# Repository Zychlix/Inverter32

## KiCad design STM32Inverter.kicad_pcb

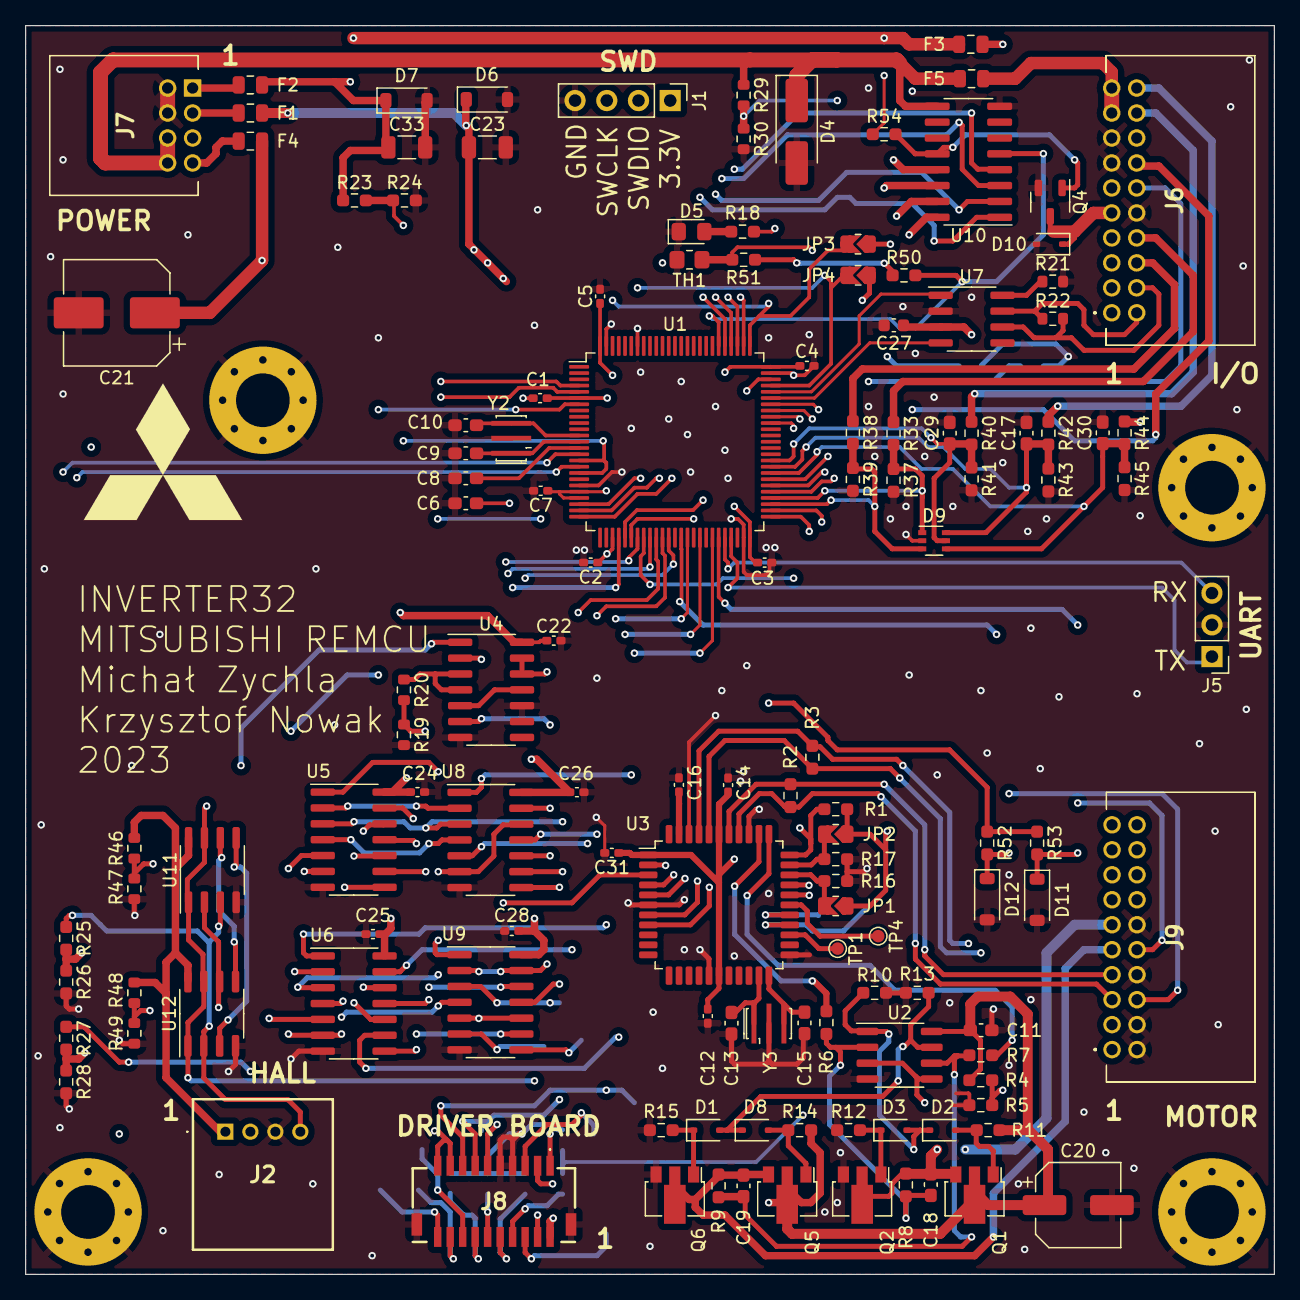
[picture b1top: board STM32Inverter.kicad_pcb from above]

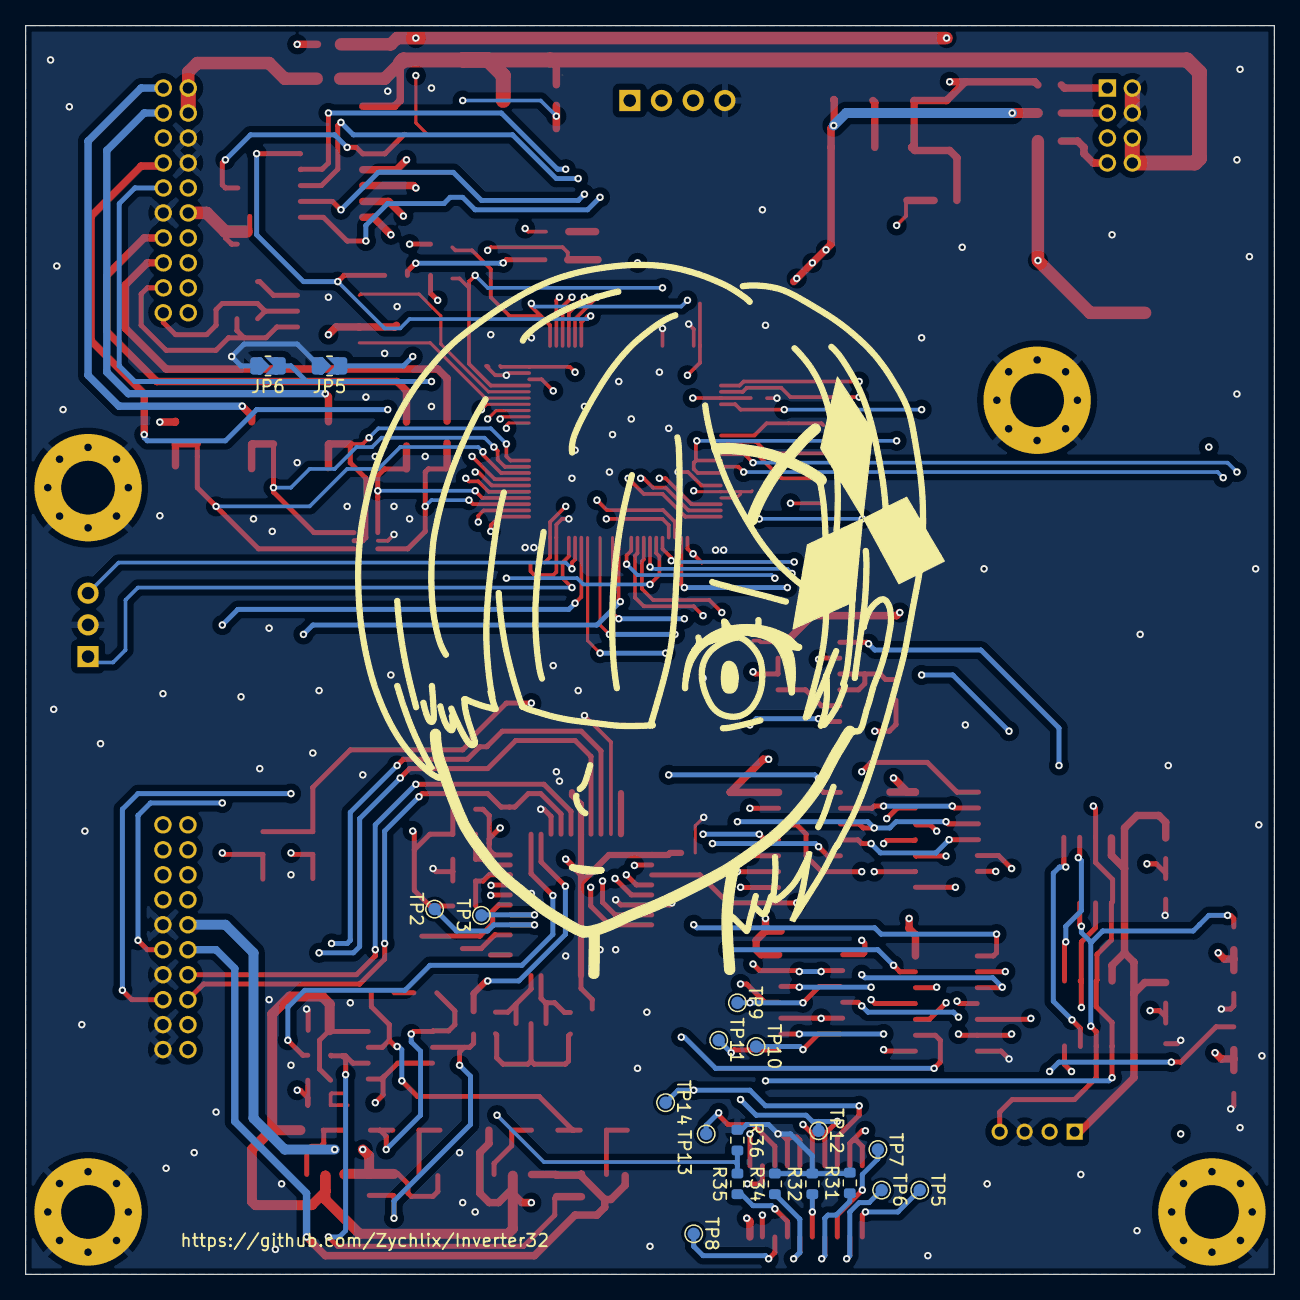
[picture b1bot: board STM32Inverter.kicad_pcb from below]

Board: 4 copper layers, 100.0 x 100.0 mm, 154 parts (19 on the bottom side), 137 nets.

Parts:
C1, C2, C3, C4, C5, C7, C12, C14, C16, C22, C24, C25, C26, C28, C31: 1u; C_0402_1005Metric_Pad0.74x0.62mm_HandSolder
C6: 10n; C_0603_1608Metric_Pad1.08x0.95mm_HandSolder
C8, C11, C17, C29, C30: 100n; C_0603_1608Metric_Pad1.08x0.95mm_HandSolder
C9, C10, C13, C15: DNP; C_0603_1608Metric_Pad1.08x0.95mm_HandSolder
C18, C19: 100p; C_0603_1608Metric_Pad1.08x0.95mm_HandSolder
C20: 100u; CP_Elec_6.3x7.7
C21: 100uF 25V; CP_Elec_8x6.2
C23, C33: 22uF 10V; C_1206_3216Metric
C27: 100nF; C_0603_1608Metric
D1, D2, D3, D8, D10: 1N4148; D_SOD-323
D4: 1N4007; D_SMA_Handsoldering
D5: LED; LED_0805_2012Metric_Pad1.15x1.40mm_HandSolder
D6, D11, D12: BZT52C3V6; D_SOD-123
D7: BZT52C5V6; D_SOD-123
D9: PESD3V3L5UY; SOT-363_SC-70-6
F1, F2, F3, F4: 350mA; Fuse_0805_2012Metric
F5: 2A; Fuse_0805_2012Metric
H1, H2, H3, H4: MountingHole_Pad; MountingHole_4.3mm_M4_Pad_Via
J1: STLINK; PinHeader_1x04_P2.54mm_Vertical
J2: CURRENT SENSE; DF51K4P2DS805
J5: UART; PinHeader_1x03_P2.54mm_Vertical
J6: INTERFACE; DF51K20DP2DS805
J7: POWER; DF51K8DP2DS805
J8: 501571-2007; 5015712007
J9: RESOLVER; DF51K20DP2DS805
JP1, JP2, JP3, JP4, JP5, JP6: R_0805_2012Metric_Jumper
Q1, Q5: BCX54; SOT-89-3
Q2, Q6: BCX55; SOT-89-3
Q4: ST3422A; SOT-23-3
R1: 4.7k; R_0603_1608Metric_Pad0.98x0.95mm_HandSolder
R2, R3: 68k; R_0603_1608Metric_Pad0.98x0.95mm_HandSolder
R4, R5: 22k; R_0603_1608Metric_Pad0.98x0.95mm_HandSolder
R6, R7, R8, R9, R16, R17, R23, R24, R25, R26, R27, R28, R33, R37, R38, R39, R40, R42, R44, R51, R52, R53: 10k; R_0603_1608Metric_Pad0.98x0.95mm_HandSolder
R10, R11, R12, R13, R14, R15, R41, R43, R45, R50, R54: 2.2k; R_0603_1608Metric_Pad0.98x0.95mm_HandSolder
R18: 470; R_0603_1608Metric_Pad0.98x0.95mm_HandSolder
R19, R30, R31, R32, R34, R36: 4.7k; R_0603_1608Metric
R20, R29, R35: 2.7k; R_0603_1608Metric
R21: 1k; R_0603_1608Metric
R22: 120; R_0603_1608Metric
R46, R47, R48, R49: R_0603_1608Metric
TH1: Thermistor_NTC; R_0805_2012Metric_Pad1.20x1.40mm_HandSolder
TP1: A; TestPoint_Pad_D1.0mm
TP2: B; TestPoint_Pad_D1.0mm
TP3: NM; TestPoint_Pad_D1.0mm
TP4: DIR; TestPoint_Pad_D1.0mm
TP5, TP6, TP7, TP8, TP9, TP10, TP11, TP12, TP13, TP14: TestPoint; TestPoint_Pad_D1.0mm
U1: STM32F303VCTx; LQFP-100_14x14mm_P0.5mm
U2: LM358; SO-8_3.9x4.9mm_P1.27mm
U3: AD2S1205; LQFP-44_10x10mm_P0.8mm
U4: 74HCT00; SOIC-14_3.9x8.7mm_P1.27mm
U5: 74HCT04; SOIC-14_3.9x8.7mm_P1.27mm
U6, U8, U9: 74HCT08; SOIC-14_3.9x8.7mm_P1.27mm
U7: MCP2551-I-SN; SOIC-8_3.9x4.9mm_P1.27mm
U10: ULN2002; SOP-16_3.9x9.9mm_P1.27mm
U11, U12: LM393; SO-8_3.9x4.9mm_P1.27mm
Y2, Y3: CSTNE8M00GH5C000R0; Resonator_SMD_Murata_CSTxExxV-3Pin_3.0x1.1mm_HandSoldering

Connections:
+3V3: C1.1, C2.1, C3.1, C4.1, C5.1, C6.1, C7.1, C23.1, D6.1 (K), F1.1, J1.1, R50.1, R51.1, R52.1, R53.1, U1.6 (VBAT), U1.21 (VREF+), U1.22 (VDDA), U1.28 (VDD), U1.50 (VDD), U1.75 (VDD), U1.100 (VDD)
+5V: C12.1, C14.1, C22.1, C24.1, C25.1, C26.1, C27.1, C28.1, C31.1, C33.1, D7.1 (K), F2.1, F3.1, J2.1, J8.17, J8.19, JP1.2, JP2.2, R1.1, R23.1, R46.1, R48.1, R54.1, U3.1 (DVDD), U3.17 (DVDD), U3.39 (AVdd), U4.14 (VCC), U5.14 (VCC), U6.14 (VCC), U7.3 (VDD), U8.14 (VCC), U9.14 (VCC), U11.8 (V+), U12.8 (V+)
+5VA: J7.5, J8.2
+12_EXT: F5.2, J6.17, J6.19
+12_UNSTABILIZED: D4.1 (K), F5.1, J7.6, J7.8, R29.1, U10.9 (COM)
+15V: C11.1, C20.1, C21.1, F4.1, Q1.2 (C), Q5.2 (C), R4.2, R11.1, R14.1, U2.8 (V+)
/2.5V: R23.2, R24.1, U1.16 (PC1), U1.18 (PC3)
/+12_EXT_ADC: R29.2, R30.1, U1.56 (PD9)
/ACC_INPUT_A_3V3: D9.1 (K1), R33.2, R37.1, U1.54 (PB15)
/ACC_INPUT_B_3V3: D9.3 (K2), R38.2, R39.1, U1.53 (PB14)
/AD2S1205/EXC: R7.1, U3.34 (EXC)
/AD2S1205/Vcc/2: R4.1, R5.2, U2.3 (+), U2.5 (+)
/AD2S1205/~EXC: R6.1, U3.35 (~EXC)
/AUX_IN: C30.1, D9.4 (K3), R44.2, R45.1, U1.58 (PD11)
/BRK_IN: C29.1, D9.5 (K4), R40.2, R41.1, U1.60 (PD13)
/CAN_H: J6.2, R22.1, U7.7 (CANH)
/CAN_L: J6.4, R22.2, U7.6 (CANL)
/CAN_RX: U1.70 (PA11), U7.4 (RXD)
/CAN_TX: U1.71 (PA12), U7.1 (TXD)
/CLK_IN: C10.1, U1.12 (PF0), Y2.3
/CLK_OUT: C9.1, U1.13 (PF1), Y2.1
/COS_H: J9.1, R3.2, U3.41 (Cos)
/COS_L: J9.3, R3.1, U3.40 (CosLO)
/CS_RES: U1.29 (PA4), U3.3 (~CS)
/CURRENT_A: R27.2, R28.1, U1.15 (PC0)
/CURRENT_A_RAW: J2.2, R27.1, U11.6 (-), U12.5 (+)
/CURRENT_B: R25.2, R26.1, U1.17 (PC2)
/CURRENT_B_RAW: J2.4, R25.1, U11.3 (+), U12.2 (-)
/DOS: U1.52 (PB13), U3.29 (DOS)
/EXC: C19.2, J9.9, Q5.3 (E), Q6.2 (C), R9.2
/FAN_OUT: U1.79 (PC11), U10.2 (I2)
/FAN_OUT_OD: J6.5, U10.15 (O2)
/FAULT_DRV: J8.4, U4.1, U11.1, U11.7, U12.1, U12.7
/FAULT_RST: U1.5 (PE6), U4.12, U4.13
/FAULT_SR_3V3: R19.1, R20.2, U1.4 (PE5)
/GPIO_A: J9.19, U1.69 (PA10)
/GPIO_B: J9.17, U1.68 (PA9)
/GPIO_C: J9.15, U1.67 (PA8)
/GPIO_D: J9.13, U1.66 (PC9)
/KEY_IN: C17.1, D9.6 (K5), R42.2, R43.1, U1.59 (PD12)
/LED_PIN: R18.1, U1.73 (PF6)
/LOT: U1.51 (PB12), U3.30 (LOT)
/MAIN_OUT: R50.2, U1.81 (PD0), U10.5 (I5)
/MAIN_OUT_OD: D10.1 (K), J6.9, Q4.3 (D)
/MISO_RES: U1.31 (PA6), U3.7 (DB11/SO)
/NEG_CURRENT_SETPOINT: R46.2, R47.1, U11.5 (+), U12.3 (+)
/POS_CURRENT_SETPOINT: R48.2, R49.1, U11.2 (-), U12.6 (-)
/PRECHARGE_OUT: U1.78 (PC10), U10.3 (I3)
/PRECHARGE_OUT_OD: J6.7, U10.14 (O3)
/PUMP_OUT: U1.80 (PC12), U10.1 (I1)
/PUMP_OUT_OD: J6.3, U10.16 (O1)
/PWM_CH1: U1.40 (PE9), U6.1
/PWM_CH1N: U1.7 (PC13), U6.5
/PWM_CH2: U1.42 (PE11), U6.9
/PWM_CH2N: U1.35 (PB0), U6.13
/PWM_CH3: U1.44 (PE13), U8.1
/PWM_CH3N: U1.36 (PB1), U8.5
/PWM_DRIVER/DRIVER_OUTPUT_ENABLE: U4.2, U4.6, U8.10, U8.13, U9.2, U9.5, U9.10, U9.13
/RD: U1.23 (PA0), U3.2 (~RD)
/RDVEL: U1.25 (PA2), U3.5 (~RDVEL)
/SAMPLE: U1.24 (PA1), U3.4 (~SAMPLE)
/SCLK_RES: U1.30 (PA5), U3.8 (DB10)
/SIN_H: J9.5, R2.1, U3.37 (Sin)
/SIN_L: J9.7, R2.2, U3.38 (SinLO)
/SWCLK: J1.3, JP3.1, U1.76 (PA14)
/SWDIO: J1.2, JP4.1, U1.72 (PA13)
/T1_DRV: J8.10, R34.1, U1.37 (PB2)
/T2_DRV: J8.12, R32.1, U1.34 (PC5)
/T3_DRV: J8.14, R31.1, U1.32 (PA7)
/TEMP_INTERNAL: R51.2, TH1.1, U1.57 (PD10)
/TH1: D12.1 (K), J9.6, R52.2, U1.39 (PE8)
/TH2: D11.1 (K), J9.10, R53.2, U1.45 (PE14)
/USART3_RX: J5.3, U1.46 (PE15)
/USART3_TX: J5.1, U1.47 (PB10)
/U_HIGH: J8.1, TP9.1, U9.3
/U_LOW: J8.11, TP10.1, U9.6
/VBUS_DRV: R35.2, R36.1, U1.55 (PD8)
/V_HIGH: J8.5, TP13.1, U8.8
/V_LOW: J8.15, TP14.1, U8.11
/W_HIGH: J8.3, TP11.1, U9.8
/W_LOW: J8.13, TP12.1, U9.11
/X_OUT: U1.77 (PA15), U10.4 (I4)
/X_OUT_OD: J6.11, U10.13 (O4)
/~EXC: C18.2, J9.11, Q1.3 (E), Q2.2 (C), R8.2
/~RESET_RES: R1.2, U1.33 (PC4), U3.33 (~RESET)
GND: C1.2, C2.2, C3.2, C4.2, C5.2, C6.2, C7.2, C8.2, C9.2, C10.2, C11.2, C12.2, C13.2, C14.2, C15.2, C16.2, C17.2, C20.2, C21.2, C22.2, C23.2, C24.2, C25.2, C26.2, C27.2, C28.2, C29.2, C30.2, C31.2, C33.2, D4.2 (A), D5.1 (K), D6.2 (A), D7.2 (A), D9.2 (A), D10.2 (A), D11.2 (A), D12.2 (A), H1.1, H2.1, H3.1, H4.1, J1.4, J2.3, J5.2, J6.10, J6.13, J6.15, J7.2, J7.4, J8.7, J8.9, J8.MP1, J8.MP2, J9.2, J9.4, J9.8, J9.12, JP5.2, JP6.2, Q2.3 (E), Q4.2 (S), Q6.3 (E), R5.1, R10.2, R12.2, R13.2, R15.2, R16.2, R17.2, R19.2, R21.2, R24.2, R26.2, R28.2, R30.2, R31.2, R32.2, R34.2, R36.2, R37.2, R39.2, R41.2, R43.2, R45.2, R47.2, R49.2, TH1.2, U1.20 (VSSA), U1.49 (VSS), U1.74 (VSS), U1.94 (BOOT0), U1.99 (VSS), U2.4 (V-), U3.6 (~SOE), U3.16 (GND), U3.23 (GND), U3.36 (AGND), U3.42 (AGND), U4.7 (GND), U4.9, U4.10, U5.7 (GND), U6.7 (GND), U7.2 (VSS), U8.7 (GND), U9.7 (GND), U10.8 (GND), U11.4 (V-), U12.4 (V-), Y2.2, Y3.2
unnamed: D1.2 (A), D8.1 (K), R13.1, U2.7
unnamed: D1.1 (K), Q6.1 (B), R15.1
unnamed: D2.2 (A), Q1.1 (B), R11.2
unnamed: D2.1 (K), D3.2 (A), R10.1, U2.1
unnamed: D3.1 (K), Q2.1 (B), R12.1
unnamed: D5.2 (A), R18.2
unnamed: D8.2 (A), Q5.1 (B), R14.2
unnamed: F1.2, J7.3
unnamed: F2.2, J7.1
unnamed: F3.2, J6.16
unnamed: F4.2, J7.7
unnamed: J6.1, R44.1
unnamed: J6.6, R38.1
unnamed: J6.8, R33.1
unnamed: J6.12, JP4.2, JP6.1
unnamed: J6.14, JP3.2, JP5.1
unnamed: J6.18, R40.1
unnamed: J6.20, R42.1
unnamed: J8.6, TP8.1
unnamed: J8.8, R35.1
unnamed: J8.16, TP7.1
unnamed: J8.18, TP6.1
unnamed: J8.20, TP5.1
unnamed: Q4.1 (G), R54.2, U10.12 (O5)
unnamed: R20.1, U4.3, U4.4
unnamed: C8.1, U1.14 (NRST)
unnamed: C18.1, R6.2, R8.1, U2.2 (-)
unnamed: C19.1, R7.2, R9.1, U2.6 (-)
unnamed: TP1.1, U3.25 (A)
unnamed: TP2.1, U3.26 (B)
unnamed: C15.1, U3.22 (CLKIN), Y3.3
unnamed: TP4.1, U3.28 (DIR)
unnamed: JP1.1, R16.1, U3.31 (FS1)
unnamed: JP2.1, R17.1, U3.32 (FS2)
unnamed: TP3.1, U3.27 (NM)
unnamed: C16.1, U3.43 (REFBYP)
unnamed: C13.1, U3.21 (XTALOUT), Y3.1
unnamed: U4.5, U4.11
unnamed: U5.1, U8.6, U8.12
unnamed: U5.2, U8.2
unnamed: U5.3, U8.3, U8.9
unnamed: U5.4, U8.4
unnamed: U5.5, U6.6, U9.4
unnamed: U5.6, U6.2
unnamed: U5.8, U6.4
unnamed: U5.9, U6.3, U9.1
unnamed: U5.10, U6.10
unnamed: U5.11, U6.11, U9.12
unnamed: U5.12, U6.12
unnamed: U5.13, U6.8, U9.9
unnamed: R21.1, U7.8 (Rs)

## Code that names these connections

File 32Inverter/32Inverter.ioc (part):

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Mcu.Name=STM32F303V(B-C)Tx
Mcu.Package=LQFP100
Mcu.UserName=STM32F303VCTx
PA0.GPIOParameters=GPIO_Speed,GPIO_Label
PA0.GPIO_Label=RD
PA0.GPIO_Speed=GPIO_SPEED_FREQ_HIGH
PA0.Signal=GPIO_Output
PA1.GPIOParameters=GPIO_Speed,GPIO_Label
PA1.GPIO_Label=SAMPLE
PA1.GPIO_Speed=GPIO_SPEED_FREQ_HIGH
PA1.Signal=GPIO_Output
PA10.GPIOParameters=GPIO_Speed,GPIO_Label
PA10.GPIO_Label=GPIO_A
PA10.GPIO_Speed=GPIO_SPEED_FREQ_HIGH
PA10.Signal=GPIO_Output
PA11.Mode=CAN_Activate
PA11.Signal=CAN_RX
PA12.Mode=CAN_Activate
PA12.Signal=CAN_TX
PA15.GPIOParameters=GPIO_Speed,GPIO_PuPd,GPIO_Label,GPIO_ModeDefaultOutputPP
PA15.GPIO_Label=X_OUT
PA15.GPIO_ModeDefaultOutputPP=GPIO_MODE_OUTPUT_OD
PA15.GPIO_PuPd=GPIO_NOPULL
PA15.GPIO_Speed=GPIO_SPEED_FREQ_HIGH
PA15.Signal=GPIO_Output
PA2.GPIOParameters=GPIO_Speed,GPIO_Label
PA2.GPIO_Label=RDVEL
PA2.GPIO_Speed=GPIO_SPEED_FREQ_HIGH
PA2.Signal=GPIO_Output
PA4.GPIOParameters=GPIO_Speed,GPIO_Label
PA4.GPIO_Label=CS_RES
PA4.GPIO_Speed=GPIO_SPEED_FREQ_HIGH
PA4.Signal=GPIO_Output
PA5.Mode=RX_Only_Simplex_Unidirect_Master
PA5.Signal=SPI1_SCK
PA6.Mode=RX_Only_Simplex_Unidirect_Master
PA6.Signal=SPI1_MISO
PA7.GPIOParameters=GPIO_Label
PA7.GPIO_Label=T3
PA7.Mode=IN4-Single-Ended
PA7.Signal=ADC2_IN4
PA8.GPIOParameters=GPIO_Speed,GPIO_Label
PA8.GPIO_Label=GPIO_C
PA8.GPIO_Speed=GPIO_SPEED_FREQ_HIGH
PA8.Signal=GPIO_Output
PA9.GPIOParameters=GPIO_Speed,GPIO_Label
PA9.GPIO_Label=GPIO_B
PA9.GPIO_Speed=GPIO_SPEED_FREQ_HIGH
PA9.Signal=GPIO_Output
PB0.GPIOParameters=GPIO_PuPd
PB0.GPIO_PuPd=GPIO_PULLDOWN
PB0.Mode=PWM Generation2 CH2 CH2N
PB0.Signal=TIM1_CH2N
PB1.GPIOParameters=GPIO_PuPd
PB1.GPIO_PuPd=GPIO_PULLDOWN
PB1.Mode=PWM Generation3 CH3 CH3N
PB1.Signal=TIM1_CH3N
PB10.Mode=Asynchronous
PB10.Signal=USART3_TX
PB12.GPIOParameters=GPIO_Label
PB12.GPIO_Label=LOT_IN
PB12.Signal=GPIO_Input
PB13.GPIOParameters=GPIO_Label
PB13.GPIO_Label=DOS_IN
PB13.Signal=GPIO_Input
PB14.GPIOParameters=GPIO_Label
PB14.GPIO_Label=ADC_IN_B
PB14.Mode=IN4-Single-Ended
PB14.Signal=ADC4_IN4
PB15.GPIOParameters=GPIO_Label
PB15.GPIO_Label=ADC_IN_A
PB15.Mode=IN5-Single-Ended
PB15.Signal=ADC4_IN5
PB2.GPIOParameters=GPIO_Label
PB2.GPIO_Label=T1
PB2.Mode=IN12-Single-Ended
PB2.Signal=ADC2_IN12
PC0.GPIOParameters=GPIO_Label
PC0.GPIO_Label=CURR_A+
PC0.Signal=ADCx_IN6
PC1.GPIOParameters=GPIO_Label
PC1.GPIO_Label=CURR_A-
PC1.Signal=ADCx_IN7
PC10.GPIOParameters=GPIO_Speed,GPIO_Label
PC10.GPIO_Label=PRECHARGE_OUT
PC10.GPIO_Speed=GPIO_SPEED_FREQ_HIGH
PC10.Signal=GPIO_Output
PC11.GPIOParameters=GPIO_Speed,GPIO_Label
PC11.GPIO_Label=FAN_OUT
PC11.GPIO_Speed=GPIO_SPEED_FREQ_HIGH
PC11.Signal=GPIO_Output
PC12.GPIOParameters=GPIO_Speed,GPIO_Label
PC12.GPIO_Label=PUMP_OUT
PC12.GPIO_Speed=GPIO_SPEED_FREQ_HIGH
PC12.Signal=GPIO_Output
PC13.GPIOParameters=GPIO_PuPd
PC13.GPIO_PuPd=GPIO_PULLDOWN
PC13.Mode=PWM Generation1 CH1 CH1N
PC13.Signal=TIM1_CH1N
PC2.GPIOParameters=GPIO_Label
PC2.GPIO_Label=CURR_B+
PC2.Signal=ADCx_IN8
PC3.GPIOParameters=GPIO_Label
PC3.GPIO_Label=CURR_B-
PC3.Signal=ADCx_IN9
PC4.GPIOParameters=GPIO_Speed,GPIO_Label
PC4.GPIO_Label=RESET_RES
PC4.GPIO_Speed=GPIO_SPEED_FREQ_HIGH
PC4.Signal=GPIO_Output
PC5.GPIOParameters=GPIO_Label
PC5.GPIO_Label=T2
PC5.Mode=IN11-Single-Ended
PC5.Signal=ADC2_IN11
PC9.GPIOParameters=GPIO_Speed,GPIO_Label
PC9.GPIO_Label=GPIO_D
PC9.GPIO_Speed=GPIO_SPEED_FREQ_HIGH
PC9.Signal=GPIO_Output
PD0.GPIOParameters=GPIO_Speed,GPIO_Label
PD0.GPIO_Label=MAIN_OUT
PD0.GPIO_Speed=GPIO_SPEED_FREQ_HIGH
PD0.Signal=GPIO_Output
PD8.GPIOParameters=GPIO_Label
PD8.GPIO_Label=VBUS
PD8.Mode=IN12-Single-Ended
PD8.Signal=ADC4_IN12
PD9.GPIOParameters=GPIO_Label
PD9.GPIO_Label=ADC_12V
PD9.Mode=IN13-Single-Ended
PD9.Signal=ADC4_IN13
PE11.GPIOParameters=GPIO_PuPd
PE11.GPIO_PuPd=GPIO_PULLDOWN
PE11.Signal=S_TIM1_CH2
PE13.GPIOParameters=GPIO_PuPd
PE13.GPIO_PuPd=GPIO_PULLDOWN
PE13.Signal=S_TIM1_CH3
PE14.GPIOParameters=GPIO_Label
PE14.GPIO_Label=TH2
PE14.Mode=IN1-Single-Ended
PE14.Signal=ADC4_IN1
PE15.Mode=Asynchronous
PE15.Signal=USART3_RX
PE5.GPIOParameters=GPIO_Label
PE5.GPIO_Label=FAULT_SR_3V3
PE5.Signal=GPIO_Input
PE6.GPIOParameters=GPIO_Speed,GPIO_Label
PE6.GPIO_Label=FAULT_RST
PE6.GPIO_Speed=GPIO_SPEED_FREQ_HIGH
PE6.Signal=GPIO_Output
PE8.GPIOParameters=GPIO_Label
PE8.GPIO_Label=TH1
PE8.Signal=ADCx_IN6P
PE9.GPIOParameters=GPIO_PuPd
PE9.GPIO_PuPd=GPIO_PULLDOWN
PE9.Signal=S_TIM1_CH1
PF0-OSC_IN.Signal=RCC_OSC_IN
PF1-OSC_OUT.Signal=RCC_OSC_OUT
PF6.GPIOParameters=GPIO_Speed,GPIO_Label
PF6.GPIO_Label=LED
PF6.GPIO_Speed=GPIO_SPEED_FREQ_HIGH
PF6.Signal=GPIO_Output
RCC.HSEPLLFreq_Value=8000000
RCC.HSE_VALUE=8000000
RCC.SYSCLKFreq_VALUE=64000000
RCC.SYSCLKSourceVirtual=RCC_SYSCLKSOURCE_PLLCLK
board=custom

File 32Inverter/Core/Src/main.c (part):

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

    GPIO_InitTypeDef GPIO_InitStruct = {0};
    GPIO_InitStruct.Pin = FAN_OUT_Pin;
    GPIO_InitStruct.Mode = GPIO_MODE_AF_PP;
    GPIO_InitStruct.Pull = GPIO_NOPULL;
    GPIO_InitStruct.Speed = GPIO_SPEED_FREQ_LOW;
    GPIO_InitStruct.Alternate = GPIO_AF4_TIM8;
    HAL_GPIO_Init(FAN_OUT_GPIO_Port, &GPIO_InitStruct);

    RCC_PeriphCLKInitTypeDef PeriphClkInit = {0};

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
void startup_relay_box_init()
{
    inv.relay_box.precharge_contactor.pin = PRECHARGE_OUT_Pin;
    inv.relay_box.precharge_contactor.port = PRECHARGE_OUT_GPIO_Port;
    inv.relay_box.main_contactor.pin = MAIN_OUT_Pin;
    inv.relay_box.main_contactor.port = MAIN_OUT_GPIO_Port;
}
void startup_gpio_init()
{
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//    HAL_GPIO_Init(GPIOB, &GPIO_InitStruct);

    HAL_GPIO_WritePin(GPIO_A_GPIO_Port, GPIO_A_Pin,
                      true); // hack for enabling the inverter, control FAULT_DRV via GPIOA

    GPIO_InitStruct.Pin = BRK_IN_PIN;
    GPIO_InitStruct.Mode = GPIO_MODE_INPUT;
    GPIO_InitStruct.Pull = GPIO_NOPULL;
    HAL_GPIO_Init(GPIOD, &GPIO_InitStruct);

    charger.power.port = PUMP_OUT_GPIO_Port;
    charger.power.pin = PUMP_OUT_Pin;
}
void startup_periph_init()
{
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    charger.can = &hcan;


    bool charger_mode = HAL_GPIO_ReadPin( BRK_IN_PORT, BRK_IN_PIN); // Checks what mode to work in

//          init charger power and whatnot
        if(chg_init(&charger)!= CHG_OK)
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    uint32_t last_call = 0;

    //Main loop
    HAL_GPIO_WritePin(PUMP_OUT_GPIO_Port,PUMP_OUT_Pin, GPIO_PIN_SET);
    while (1) {


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                chg_print_data(&charger);
                chg_send_data(&charger);

                HAL_GPIO_WritePin(PUMP_OUT_GPIO_Port,PUMP_OUT_Pin, GPIO_PIN_RESET);


                if((HAL_GetTick() -  charger.last_received_time)<1000 && !charger.telemetry.communication_timeout)
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    __HAL_RCC_GPIOD_CLK_ENABLE();

    /*Configure GPIO pin Output Level */
    HAL_GPIO_WritePin(FAULT_RST_GPIO_Port, FAULT_RST_Pin, GPIO_PIN_RESET);

    /*Configure GPIO pin Output Level */
    HAL_GPIO_WritePin(GPIOA, RD_Pin | SAMPLE_Pin | RDVEL_Pin | CS_RES_Pin
                             | GPIO_C_Pin | GPIO_B_Pin | GPIO_A_Pin | X_OUT_Pin, GPIO_PIN_RESET);

    HAL_GPIO_WritePin(GPIOA, GPIO_A_Pin, GPIO_PIN_SET);

    /*Configure GPIO pin Output Level */
    HAL_GPIO_WritePin(GPIOC, RESET_RES_Pin | GPIO_D_Pin | PRECHARGE_OUT_Pin //| FAN_OUT_Pin
                             | PUMP_OUT_Pin, GPIO_PIN_RESET);

    /*Configure GPIO pin Output Level */
    HAL_GPIO_WritePin(LED_GPIO_Port, LED_Pin, GPIO_PIN_RESET);

    /*Configure GPIO pin Output Level */
    HAL_GPIO_WritePin(MAIN_OUT_GPIO_Port, MAIN_OUT_Pin, GPIO_PIN_RESET);

    /*Configure GPIO pin : FAULT_SR_3V3_Pin */
    GPIO_InitStruct.Pin = FAULT_SR_3V3_Pin;
    GPIO_InitStruct.Mode = GPIO_MODE_INPUT;
    GPIO_InitStruct.Pull = GPIO_NOPULL;
    HAL_GPIO_Init(FAULT_SR_3V3_GPIO_Port, &GPIO_InitStruct);

    /*Configure GPIO pin : FAULT_RST_Pin */
    GPIO_InitStruct.Pin = FAULT_RST_Pin;
    GPIO_InitStruct.Mode = GPIO_MODE_OUTPUT_PP;
    GPIO_InitStruct.Pull = GPIO_NOPULL;
    GPIO_InitStruct.Speed = GPIO_SPEED_FREQ_HIGH;
    HAL_GPIO_Init(FAULT_RST_GPIO_Port, &GPIO_InitStruct);

    /*Configure GPIO pins : RD_Pin SAMPLE_Pin RDVEL_Pin CS_RES_Pin
                             GPIO_C_Pin GPIO_B_Pin GPIO_A_Pin */
    GPIO_InitStruct.Pin = RD_Pin | SAMPLE_Pin | RDVEL_Pin | CS_RES_Pin
                          | GPIO_C_Pin | GPIO_B_Pin | GPIO_A_Pin;
    GPIO_InitStruct.Mode = GPIO_MODE_OUTPUT_PP;
    GPIO_InitStruct.Pull = GPIO_NOPULL;
    GPIO_InitStruct.Speed = GPIO_SPEED_FREQ_HIGH;
    HAL_GPIO_Init(GPIOA, &GPIO_InitStruct);

    /*Configure GPIO pins : RESET_RES_Pin GPIO_D_Pin PRECHARGE_OUT_Pin FAN_OUT_Pin
                             PUMP_OUT_Pin */
    GPIO_InitStruct.Pin = RESET_RES_Pin | GPIO_D_Pin | PRECHARGE_OUT_Pin //| FAN_OUT_Pin
                          | PUMP_OUT_Pin;
    GPIO_InitStruct.Mode = GPIO_MODE_OUTPUT_PP;
    GPIO_InitStruct.Pull = GPIO_NOPULL;
    GPIO_InitStruct.Speed = GPIO_SPEED_FREQ_HIGH;
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    GPIO_InitStruct.Pull = GPIO_NOPULL;
    HAL_GPIO_Init(GPIOB, &GPIO_InitStruct);

    /*Configure GPIO pin : LED_Pin */
    GPIO_InitStruct.Pin = LED_Pin;
    GPIO_InitStruct.Mode = GPIO_MODE_OUTPUT_PP;
    GPIO_InitStruct.Pull = GPIO_NOPULL;
    GPIO_InitStruct.Speed = GPIO_SPEED_FREQ_HIGH;
    HAL_GPIO_Init(LED_GPIO_Port, &GPIO_InitStruct);

    /*Configure GPIO pin : X_OUT_Pin */
    GPIO_InitStruct.Pin = X_OUT_Pin;
    GPIO_InitStruct.Mode = GPIO_MODE_OUTPUT_PP;
    GPIO_InitStruct.Pull = GPIO_NOPULL;
    GPIO_InitStruct.Speed = GPIO_SPEED_FREQ_HIGH;
    HAL_GPIO_Init(X_OUT_GPIO_Port, &GPIO_InitStruct);

    GPIO_InitStruct.Pin = GPIO_A_Pin;
    GPIO_InitStruct.Mode = GPIO_MODE_OUTPUT_OD;
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    GPIO_InitStruct.Speed = GPIO_SPEED_FREQ_HIGH;
    HAL_GPIO_Init(GPIO_A_GPIO_Port, &GPIO_InitStruct);

    /*Configure GPIO pin : MAIN_OUT_Pin */
    GPIO_InitStruct.Pin = MAIN_OUT_Pin;
    GPIO_InitStruct.Mode = GPIO_MODE_OUTPUT_OD;
    GPIO_InitStruct.Pull = GPIO_NOPULL;
    GPIO_InitStruct.Speed = GPIO_SPEED_FREQ_HIGH;
    HAL_GPIO_WritePin(MAIN_OUT_GPIO_Port, MAIN_OUT_Pin,1);
    HAL_GPIO_Init(MAIN_OUT_GPIO_Port, &GPIO_InitStruct);

/* USER CODE BEGIN MX_GPIO_Init_2 */
/* USER CODE END MX_GPIO_Init_2 */
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{
    TIM8->SR = 0;
//    HAL_GPIO_TogglePin(GPIOB, GPIO_PIN_10);
    HAL_GPIO_WritePin(X_OUT_GPIO_Port, X_OUT_Pin,1);
    inv_auxiliary_tick(&inv);
    HAL_GPIO_WritePin(X_OUT_GPIO_Port, X_OUT_Pin,0);
//    HAL_GPIO_TogglePin(GPIOB, GPIO_PIN_10);


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
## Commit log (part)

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2023-05-07 initial
2023-05-08 Added STM32Cube file and schematic subsheets
2023-05-09 Added current sensing
2023-05-09 Connectors added
2023-05-11 Added some pin assignments
2023-05-11 Footprints
2023-05-12 Preliminary footprints
2023-05-12 A lot of changes
2023-05-12 Schematic cleanup. Pinout changed
2023-05-12 Added High current OD and comparators
2023-05-12 Fixed labels
2023-05-13 Added libraries, NTC
2023-05-14 Final version before layout
2023-05-14 Resolver layout
2023-05-14 Key exclusion layout
2023-05-14 Layout mostly done
2023-05-14 Traces almost done
2023-05-14 Board done
2023-05-14 Board enven more done
2023-05-14 Awaiting review
2023-05-14 Remove backups from git
2023-05-14 Fix DRC warnings and exclude jumper errors
2023-05-14 Hole moved
2023-05-15 Review done
2023-05-15 change holes
2023-05-15 Move T1-3 from ADC1 to ADC2\nNow ADC1 is used only for current measurment
2023-05-16 change via size to 0.6/0.3mm
2023-05-16 Added mosfet pullup to +5V
2023-05-17 added GPIO. Deploy
2023-05-17 Ordered
2023-06-09 Soft initial
2023-06-11 Zabawy z Krzysztofem. Silnik kręcony
2023-06-16 Smieci
2023-06-17 Work in progress
2023-06-17 transformaty
2023-06-17 Jest prąd
2023-06-20 Added readouts
2023-06-24 Fixed ADC readouts of VBUS and 12V
2023-06-24 Refomat
2023-06-24 Added oscilloscope, fixed current noise, added PID, added some vector functions
2023-06-24 PID zaczął troszkę działać
2023-06-24 Trud skończon
2023-07-08 Usunięcie stanów nieustalonych na starcie
2023-07-08 Gaz na potencjometrze
2023-07-08 Anti-windup, new battery,
2025-02-28 Added CLI
2025-02-28 Calibrated current shunts
2025-02-28 AB mode operational
2025-02-28 Adding AB plotting, communication errors
2025-02-28 Set encoder offset. Testing DQ
2025-03-01 Tuning PI
2025-03-01 Tuned PI Q
2025-03-01 Tuned PI D
2025-03-01 Trig lookup
2025-03-01 Use hardware FPU
2025-03-02 Designined IIR filter, added current setpoint smoothing
2025-03-02 Rename back EMF to flux_linkage
2025-03-07 Tuning PID
2025-03-07 Added ozone
2025-03-07 Trimmed speed calculation
2025-03-08 Transistor temperature readout ok, vbus reading
2025-03-08 Added filters to ADC readouts
2025-03-08 Added .gitignore
2025-03-08 Remove accidentally commited build folder
2025-03-08 Inverter enable function mod
2025-03-08 Optimizing ISR speed
2025-03-08 Increased SPI speed
2025-03-08 Added IIR
2025-03-08 Still not working phases are off
2025-03-09 Modeling
2025-03-09 robi kreske swo
2025-03-09 Jakies sensowne nastawy PIDow D i Q
2025-03-09 PID tuned a bit
2025-03-13 Change resolver offset back to -2.9
2025-03-13 CAN started working
2025-03-13 Added charger telemetry prints
2025-03-13 Added readouts and relay control
2025-03-14 Adding pwm for cp
2025-03-14 PWMN != PWM :/
2025-03-15 Po testach u mistrza
2025-03-15 Center aligned PWM
2025-03-15 ADC synchronized with TIM
2025-03-15 PID tuning
2025-03-16 fckd smth up
2025-03-18 Repaired inverter abnormal on state via switching fault out. TO BE REPAIRED. A possible electrical problem
2025-03-18 Modified contactor routine
2025-03-18 Changed Fault set pin to GPIOA
2025-03-18 Changed Fault set pin to GPIOA. Fixed uninitialized state
2025-03-18 Charger state machine
2025-03-18 Reverted printf to USART3
2025-03-18 DCDC fixes
2025-03-20 Added SPI timeout failsafe
2025-03-20 Added cli misc commands
2025-03-20 NTC readings corrected. Added VBUS workaround when lacking (NOT GOOD)
2025-03-22 deployed 1
2025-03-22 Adopting dcdc
2025-03-22 testy
2025-04-16 Last mitsubishi
2025-04-17 Dezhou charger working
2025-04-17 Added new charger cli commands
2025-04-27 Początek robienia badania impedancji silniora
2025-04-29 Developing Python library for CAN debugging
2025-05-01 Multitrack plotting
2025-05-01 Fixed plotting
2025-05-02 Further python debugger improvement. Inverter not working
2025-05-02 Jakub zrobil debugger
2025-05-02 Changed inv tick to be calculated on adc callback (doesn't work)
2025-05-03 Finally works! Vbus needs work and whatnot
2025-05-06 Cleanup
2025-05-06 New input data structure
2025-05-08 New state machine
2025-05-08 DQ Freq works
2025-05-08 Fast data logger basics work
2025-05-08 DQ voltage current Plotting is doing great
2025-05-08 DQ sweep works!
2025-05-08 D and Q analyzing works!!!
2025-05-09 Fixed critical resolver bug
2025-05-10 MTPA implementation
2025-05-11 MTPA test
2025-05-11 Testing MTPA in a bench scenario
2025-05-13 Major change in project structure
2025-05-15 debugging can current measure interference
2025-05-15 NTC Transistor values corrected
2025-05-15 MTPA made civilized
2025-05-17 Newton added
2025-05-17 MTPA with Newton works but no torque limiting
2025-05-17 Code cleanup
2025-05-17 Added throttle readout function
2025-05-18 TIM8 works 1000Hz. Further cleanup
2025-05-20 A lot of logic and state machine improvements. Added thermal protection
2025-05-20 State machine improvements
2025-05-20 Changed to car resolver setting
2025-05-21 Very strange fix of CYCCNT
2025-05-23 Charging revamp
2025-06-18 Charging command and state machine
2025-09-20 many changes
